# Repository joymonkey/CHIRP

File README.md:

# CHIRP
Hardware and firmware for a droid control system (and spinoff audio player), evolved from the little used [ShadyRC dEvolution](https://github.com/joymonkey/dEvolution/blob/master/sketches/ShadyRC_Crossfire_250211/ShadyRC_Crossfire_250211.ino) sketch that's been tried and tested over the last few years.

# CHIRP Audio Trigger
This is an advanced MP3/M4A/WAV file decoder/mixer/player, heavily inspired by the [Sparkfun/Robertsonics MP3 Trigger](https://www.sparkfun.com/mp3-trigger.html) that has been used across droid control systems since the [original Padawan PS2 days](https://astromech.net/forums/showthread.php?8354-Using-a-Wireless-PS2-controller-with-ardurino). This project covers the custom RP2350-based PCB and the code that does the audio magic.

# CHIRP Droid Control
An evolution of the previosly mentioned ShadyRC system. The intent is to use a microcontroller and ExpressLRS radio receiver to send signals/commands to the various motion, sound and lighting systems of an Astromech droid. Some goals...

- Send system status and audio file details to the operators radio transmitter via ExpressLRS telemetry packets
- Don't require re-programming just to update sounds; if sound files on the Audio Trigger change, the system knows how to roll with it
- Be controller agnostic; initially supporting EdgeTX based radio transmitter (Radiomaster Zorro), additional transmitters in the future
- Be safe but also easy to pick up; the system should police itself to some extent
- Be expandable; when new droid gizmos show up we should be able to easily implement them
- Shouldn't require the end user (droid wrangler) to know how to code or compile; all system settings configurable via the transmitter or web interface

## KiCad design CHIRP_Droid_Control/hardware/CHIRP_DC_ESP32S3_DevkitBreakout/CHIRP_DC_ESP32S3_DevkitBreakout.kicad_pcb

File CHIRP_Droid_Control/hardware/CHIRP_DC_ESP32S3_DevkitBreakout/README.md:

# CHIRP Droid Control - ESP32-S3 DevKit Breakout Board

> [!WARNING]
> **Work In Progress**: This KiCad hardware project is currently in active development and has not yet been fabricated, assembled, or hardware-verified. Pinouts, component selections, and board layouts may change without notice.

## Overview
This custom breakout board connects an ESP32-S3 DevKit module to the CHIRP Droid Control system, featuring:
- Support for wide-format ESP32-S3 DevKit boards with labeled pinouts and antenna overhang guides
- Multi-battery voltage sensing dividers (up to 3 battery inputs) with flexible WAGO 2601-1102 and 2.54mm header footprint options
- On-board high-voltage (up to 36V input) 5V step-down buck regulator (`TPS54360DDA`) with reverse-polarity and TVS transient protection
- Optional drop-in header footprint for Pololu step-down regulator modules (`D36V28F5` / `D24V22F5`)
- Dedicated 5V auxiliary outputs for peripheral modules (CHIRP Audio Trigger, ExpressLRS receiver, etc.)
- Diode backfeed isolation between external 5V and ESP32-S3 onboard USB-C 5V

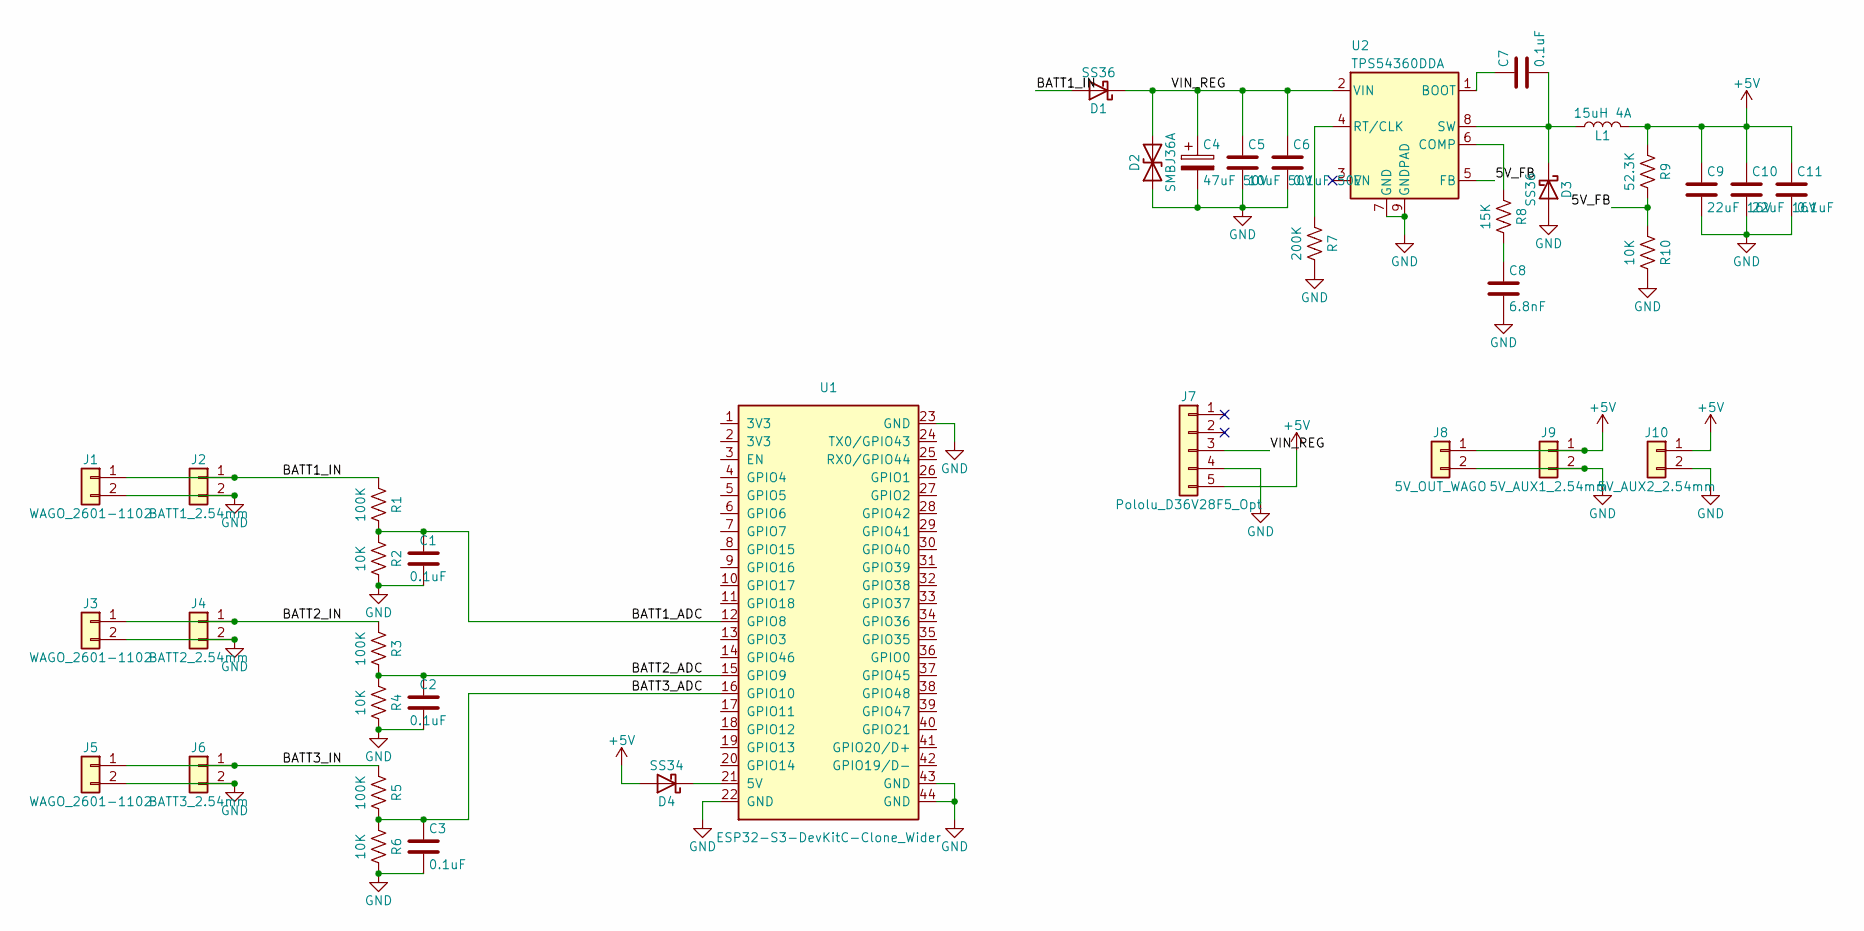
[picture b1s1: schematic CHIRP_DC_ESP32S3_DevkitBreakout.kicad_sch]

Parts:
C1, C2, C3: 0.1uF; C_0805
C4: 47uF 50V; CP_Elec_8x10.5; LCSC C2992727
C5: 10uF 50V; C_1206; LCSC C13585
C6: 0.1uF 50V; C_0805; LCSC C49678
C7, C11: 0.1uF; C_0805; LCSC C49678
C8: 6.8nF; C_0805; LCSC C1725
C9, C10: 22uF 16V; C_0805; LCSC C5674
D1, D3: SS36; D_SMA; LCSC C14996
D2: SMBJ36A; D_SMB; LCSC C123794
D4: SS34; D_SMA; LCSC C8678
J1, J3, J5: WAGO_2601-1102; WAGO_2601-1102_Horizontal
J2: BATT1_2.54mm; PinHeader_1x02_P2.54mm_Vertical
J4: BATT2_2.54mm; PinHeader_1x02_P2.54mm_Vertical
J6: BATT3_2.54mm; PinHeader_1x02_P2.54mm_Vertical
J7: Pololu_D36V28F5_Opt; Pololu_StepDown_D36V28F5_1x05_P2.54mm
J8: 5V_OUT_WAGO; WAGO_2601-1102_Horizontal
J9: 5V_AUX1_2.54mm; PinHeader_1x02_P2.54mm_Vertical
J10: 5V_AUX2_2.54mm; PinHeader_1x02_P2.54mm_Vertical
L1: 15uH 4A; L_10.4x10.4_H4.8; LCSC C169395
R1, R3, R5: 100K; R_0805
R2, R4, R6: 10K; R_0805
R7: 200K; R_0805; LCSC C17520
R8: 15K; R_0805; LCSC C17475
R9: 52.3K; R_0805; LCSC C17737
R10: 10K; R_0805; LCSC C17414
U1: ESP32-S3-DevKitC-Clone_Wider
U2: TPS54360DDA; TI_SO-PowerPAD-8_ThermalVias; LCSC C18144

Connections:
+5V: C9.1, C10.1, C11.1, D4.2 (A), J7.5, J8.1, J9.1, J10.1, L1.2, R9.1
/5V_FB: R9.2, R10.1, U2.5 (FB)
/BATT1_ADC: C1.1, R1.2, R2.1, U1.12 (GPIO8)
/BATT1_IN: D1.2 (A), J1.1, J2.1, R1.1
/BATT2_ADC: C2.1, R3.2, R4.1, U1.15 (GPIO9)
/BATT2_IN: J3.1, J4.1, R3.1
/BATT3_ADC: C3.1, R5.2, R6.1, U1.16 (GPIO10)
/BATT3_IN: J5.1, J6.1, R5.1
/VIN_REG: C4.1, C5.1, C6.1, D1.1 (K), D2.2 (A2), J7.3, U2.2 (VIN)
GND: C1.2, C2.2, C3.2, C4.2, C5.2, C6.2, C8.2, C9.2, C10.2, C11.2, D2.1 (A1), D3.2 (A), J1.2, J2.2, J3.2, J4.2, J5.2, J6.2, J7.4, J8.2, J9.2, J10.2, R2.2, R4.2, R6.2, R7.2, R10.2, U1.22 (GND), U1.23 (GND), U1.43 (GND), U1.44 (GND), U2.7 (GND), U2.9 (GNDPAD)
unnamed: C8.1, R8.2
unnamed: C7.2, D3.1 (K), L1.1, U2.8 (SW)
unnamed: D4.1 (K), U1.21 (5V)
unnamed: C7.1, U2.1 (BOOT)
unnamed: R8.1, U2.6 (COMP)
unnamed: R7.1, U2.4 (RT/CLK)

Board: 2 copper layers, 36 parts (0 on the bottom side), 16 nets, no tracks yet.

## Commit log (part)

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2026-01-05 Added USB Mass Storage Class support
    Users can now access the SD card contents via USB when MSC mode is enabled. Added serial command (MUSB:1) and GPIO pin to trigger this mode.
2026-01-05 Fixed USB freeze , added 'skip sync to flash mem' as default option
    USB MSC object construction right at the start of bootup was causing intermittent freezing. This is now deferred until startMSC() is called, to prevent USB timing problems.
    Since other users might not like the restrictions of syncing all Sound Bank 1 sound files to flash memory, I now made this an option which can be enabled in CHIRP.INI. This makes any changes to sound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
2026-01-17 Made "sync Sound Bank 1 to flash" feature optional, added MP3 support for bank 1 streams.
2026-01-17 added recent firmware UF2 file for Rev A board
2026-01-18 Added AAC support and optimizations
2026-01-18 added compiled UF2 fw file
2026-01-25 added KX vocals
    A collection of system/telemetry vocal files based on GLaDOS and KX security droids.
2026-03-04 Added fw file for RevB CHIRP Audio Trigger board
2026-03-09 embedded system sounds in code, added PVOICE command
    ### Bug Fixes: MP3/AAC Decoder & Stream Reliability
    * **Resolved Premature Audio Cutoffs**: Discovered and fixed a critical issue where the `libhelix` MP3/AAC decoders returned fewer consumed bytes than expected, silently abandoning trailing data. The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
    * **Implemented Decoder Flushing ([flush()](cci:1://file:///g:/My%20Drive/arduino/CHIRP_Droid_Control/CHIRP_Audio/msc_interface.cpp:15:0-17:1))**: The PROGMEM stream now forces the decoder to explici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
2026-05-19 added initial CHIRP Droid Control firmware and lua
2026-05-23 Added settings screen to Lua
    Moved hardcoded user settings to configurable settings via the Lua script
2026-05-25 added platformio.ini
    Changed over to building/compiling in VSCode using PlatformIO. The CHIRP Audio Trigger firmware can still be compiled in Arduino IDE by renaming main.cpp to CHIRP_Audio.ino
